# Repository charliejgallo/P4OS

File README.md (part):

# P4OS

An iPhone-style operating system for the
[**Waveshare ESP32-P4-WIFI6-Touch-LCD-5**](https://www.waveshare.com/esp32-p4-wifi6-touch-lcd-5.htm)
([wiki](https://docs.waveshare.com/ESP32-P4-WIFI6-Touch-LCD-5)). It is a 5"
720×1280 touch board with an ESP32-P4 (two RISC-V cores at 400 MHz and
32 MB of PSRAM) and an ESP32-C6 that does the Wi-Fi.

It has a home screen with pages, folders and a dock, a control centre and
notifications, and a lock screen with an optional code, and it runs in
portrait or landscape. There are twenty-three built-in apps and forty-six more on
the microSD, loaded as shared objects:

- **Games:** twenty-four, among them Mila (a Sokoban with a black cat in
  Blender 3D), Monster Hop, a racing game, golf, a robot RPG, a 3D pinball
  with six tables, a pipes game with six liquids, Doom at 35 fps and Duke
  Nukem 3D; and an emulator of
  fourteen consoles, the Game Boy Advance and the Neo Geo at full speed.
- **Tools:** notes with task lists, a street map with offline zones,
  internet radio, IP cameras, video, a 3D viewer, a tuner, a drawing app,
  a VNC viewer for a computer's screen, every 3D printer in the house
  (OctoPrint, PrusaLink, Bambu Lab, Klipper, Duet, Elegoo, FlashForge,
  Creality) with its camera, a computer algebra system with
  graphs, geometry and statistics, a data logger for the header's sensors,
  Lua, and Python (MicroPython).
- **A web portal** for files, updates, the log and the network sweeps, and a
  page for every app that wants one, which the app brings from the card.
- **Bluetooth with the phone:** the iPhone's notifications on the board, in
  colour emoji, its music, and its calls answered or rejected from the
  board; and the board as a computer's wireless keyboard and mouse.
- **USB:** the port becomes a keyboard, mouse, gamepad, MIDI device, network
  or disk for a computer; and the board is a USB host on its 40-pin header,
  two ports at once: pendrives, keyboards, mice, gamepads, webcams, sound
  cards, MIDI and serial devices.
- **A Wi-Fi network of its own,** joined with a QR code.
- **Ethernet, for a board that has the module:** a W5500 on the header,
  and tools for a wired bench: a tester for a network port, finding a
  device of unknown address, a capture for Wireshark.
- **The workshop:** I2C, SPI, 1-Wire and GPIO on the 40-pin header, with
  112 kinds of sensor read by themselves (temperature, pressure, air
  quality, light, motion, current, distance...), addressable LED strips on
  any free pin (WLED's way), a serial terminal, an ESP32, Arduino and SWD programmer,
  RS485 with a Modbus tester (master, slave, monitor, a TCP gateway) and
  DMX512 (a test console, an analyzer, RDM, an Art-Net and sACN node, and a
  lighting console for a phone), a bench supply and scope, an EEPROM reader and writer, a PWM and
  servo generator with an analog level (and sixteen more servos on a
  PCA9685), a learning
  infrared remote with SmartIR's codes, and a CAN bus analyser. Each one
  was tried on the bench with real parts, wiring diagrams and photos
  included.
- **A software radio:** an RTL-SDR stick on the USB host gives a live
  spectrum and waterfall, broadcast FM in stereo, AM for the airband and
  narrow FM for hams and PMR, and the 433/868 MHz remotes and weather
  sensors decoded, with recordings of all of it and a page in the portal.

A desktop simulator runs the same UI code, so most of it can be built and
tried without the board.

It descends from [AmoledOS](https://github.com/charliejgallo/ESP32S3_AmoledOS),
a smartwatch firmware for a 1.8" board. The app model, the portal and many
of the apps came from there, redrawn for a screen five times larger.

<p align="center"><em>The captures come from the simulator, which draws the
same pixels as the board.</em></p>

<p align="center"><em>And on the board: a BME280 on the rear header, found by
itself in Modules and by the scan in Bus, and the SPI loopback at 40 MHz
(that one is a capture from the panel, over HTTP).</em></p>

<p align="center"><em>A MAX6675 with a type K thermocouple on the SPI port:
Bus's example reads it, and Modules logs it every second; the curve is the
tip heated with a lighter.</em></p>

<p align="center"><em>A Pimoroni BME688 on i2c.ext: Bus lists what may live at
0x76, and Modules recognises it by itself as a BME688 (not a BME680), with
its gas resistance, which fell to half with alcohol near it and came back.</em></p>

<p align="center"><em>An SCD41 found by itself at 0x62: the chart is the CO2
of a breath on it, from 3000 ppm back to the room's 600.</em></p>

<p align="center"><em>The Programmer reading the whole flash of an AmoledOS
watch (an ESP32-S3 on its own USB) to the card, and writing it back: the
watch came back with every setting it had.</em></p>

<p align="center"><em>And by SWD, three wires to a Pico's debug header: the
RP2040 found behind its multidrop port and a new firmware written and
verified in under half a second.</em></p>

<p align="center"><em>A cheap Wi-Fi camera (a Hi3518EV200) opened up, its
console pads soldered to the header: U-Boot stopped with a mix of keys and its
16 MB read out through its own commands, twice, with the same SHA-256 -
the copy kept before giving it a new firmware.</em></p>

<p align="center"><em>The Ekoparty 2026 badge (an nRF52840 running
Meshtastic) read whole by SWD in 8 seconds, and an Arduino Nano from a
drawer on the USB host: written by the Programmer, then talking in the
Terminal.</em></p>

<p align="center"><em>A Blue Pill by SWD: its chip a clone (DPIDR 2BA01477,
a CKS32) with 128 KB that really are there. Read whole in a second, written
and erased; and the same again through ST's serial bootloader on the same
two wires.</em></p>

<p align="center"><em>An ESP32 DevKit on the header with six wires: the
board resets it into its ROM by itself and writes it at up to 921600 baud;
the Mac's esptool does the same through the board's bridge.</em></p>

<p align="center"><em>The same Nano, now on the header: its 5 V TX through
a divider, the EN line on its reset. Written and read by the Flasher, and
by avrdude on the Mac through the bridge.</em></p>

<p align="center"><em>A Mega 2560 from an old 3D printer and a Pro Micro on
the USB host: the Mega's own bootloader, and the Pro Micro's, reached with
the 1200-baud touch.</em></p>

<p align="center"><em>An Arduino Yún: its Linux in the Terminal through the
32U4, and its old U-Boot (no sf, no crc32, a big-endian MIPS) read whole by
the Programador, the same MD5 its Linux gives.</em></p>

<p align="center"><em>Ethernet: a W5500 Lite on the header with six loose
wires, and Network's Cable tab telling what the port it is plugged into
gives (the network's addresses are blurred).</em></p>

---

## What it does

### The shell

The home screen has icon pages, folders, a dock and widgets.

- **Arranging it** is as on an iPhone. A long press starts edit mode, where
  a swipe still turns the page and an icon held still for a moment drags:
  - onto another page;
  - onto another app, to make a folder;
  - into a folder;
  - in or out of the dock, where the icons drag the same way.

  Folders show twelve apps a page, and a swipe turns one whole page. The
  portal's `#inicio` page does the same from a computer.

- **Widgets** (on the board since 0.22.0): edit mode's **+ Widget** adds
  the clock, the sensors, Home Assistant, the system monitor or Claude's
  usage; a tap on a widget opens its sheet, with its size (2×2, 4×2, 4×4),
  what it shows and a way to take it off, and one held still for a moment
  drags like an icon. The **sensors widget** shows up to six of the sensor
  service's values (on its own CO₂, temperature, humidity, pressure and the
  like; CO₂ and particles coloured by their level), the **Home Assistant**
  one up to eight entities, the favourites or the ones picked.

- **Swiping down** from the top opens the control centre (Wi-Fi, Bluetooth,
  do not disturb, the system sounds, orientation, brightness, volume, the
  music playing on the board or on the iPhone, the screen recording) and the
  notifications, with the phone's own actions.
- **System sounds:** a few notes of the speaker's bell when locking and
  unlocking, for notifications and calls, screenshots and recordings, and an
  optional keyboard click. The control centre's bell turns them all off.
- **Recording the screen** (since 0.21.5): the control centre's Grabar
  button records what the panel shows to an MP4 on the card (`/videos`),
  games and cameras included, with a red dot in the status bar while it
  runs. The P4's own engines do the work: the PPA turns each frame into
  the encoder's YUV, the hardware H.264 encoder compresses it (70 ms a
  frame between them, 15 fps on a quiet screen and 7-9 while apps move),
  and the CPU mostly waits. It plays on a Mac or a phone as it is.
- **Typing** (since 0.24.0): the field being edited shows a blinking cursor
  and a ring in the accent colour. The keyboard has an ñ, holding a key
  opens its accents (á, ü, ñ, ¿...), shift gives one capital or locks with
  two taps, and dragging along the space bar moves the cursor. Holding a
  field selects, cuts, copies and pastes; the clipboard is shared with the
  apps and with the portal, which can type a long password or an address
  straight into the field open on the board.
- **Search** (since 0.24.0): a swipe down from the middle of the home screen
  finds apps, the pages of Settings, notes by their text and the card's
  files, and works out a sum typed in.
- **The status bar** shows the Wi-Fi or the board's own network, the card
  and the USB.
- **The orientation** is chosen in Settings or the control centre, because
  the board has no accelerometer. Apps that only make sense one way turn the
  screen while they are open.
- **The BOOT button** goes home with a tap and takes a screenshot with a long
  press; screenshots go to an album in Photos. Held during the boot screen,
  it starts in safe mode, without the card's apps.

| Settings in landscape | Macro pad | Photos |
|---|---|---|
|  |  |  |

<p align="center">
  
</p>

<p align="center"><em>Recorded by the board itself with its control
centre's button: the home screen, a folder, Photos.</em></p>

### The lock screen

It shows the time and date large, the messages that came in, and the music
playing with its buttons, over the wallpaper. To unlock, swipe up from
anywhere: the screen follows the finger.

- **When it locks:** at boot, and when the screen has been off for the time
  chosen in Settings (as soon as it goes off, or 1, 5, 15 or 60 minutes
  later). It is checked while the screen is still dark, so waking never
  shows a frame of what was under it.
- **An optional code** of 4 or 6 digits. It is kept as a salted SHA-256,
  never as itself. After 5 wrong tries the pad waits 30 s, and twice as long
  every 3 more; the count survives a restart.
- **A forgotten code:** in the BOOT button's safe mode the lock screen
  does not ask for it, and Settings can remove it.
- **Messages:** today the apps' notifications; the phone's over Bluetooth and
  Home Assistant's will arrive in the same list. With a code, their text can
  stay hidden until unlocked.

| Locked | The code | Settings, Wi-Fi: its own network |
|---|---|---|
|  |  |  |

### Wallpapers

Eight gradients and a ninth that follows the time of day (night, dawn, day,
dusk, a little different every minute), and over them a photo from the card for the home screen
and another for the lock screen, chosen from Photos (the palette at the top
right of a photo). Each is cropped to the screen, kept in PSRAM (1.8 MB a
screen, nothing in internal RAM) and darkened as much as its own
brightness asks, once, while it is decoded, so the white names read on it
with no translucent layer to blend each frame. Turning the screen crops it
again; Settings, Wallpaper shows which photo each has and removes it.
The lock screen can take a whole folder instead (since 0.22.0): another of
its photos, at random, every time the board locks. The home screen's photo
stays in PSRAM with an app in front, so going home shows it at once; the
lock screen's is let go and decoded again as the screen goes dark.

| Home, over a photo | Locked, over another |
|---|---|
|  |  |

<p align="center"><em>Both on the board, both of Mila.</em></p>

The same page picks the **accent colour** (switches, selections, the active
buttons), one of iOS's nine system colours. The lock screen's clock is
large or medium, at the top or in the middle, and white, the accent, or the
lock photo's own colour lightened (Settings, Lock screen).

The gesture is a free swipe up, as phones do it today, and not a control
dragged along a track: Apple's 2005 patent on the latter
([US 7,657,849](https://patents.google.com/patent/US7657849B2)) expired in
2025, but that is not the reason this one was chosen.

### Built-in apps

Every day:

| Files | Photos | Music | Clock | Calendar |
|---|---|---|---|---|
|  |  |  |  |  |

| Calculator | Converter | Home Assistant | Claude | Monitor |
|---|---|---|---|---|
|  |  |  |  |  |

- **Files:** the card's explorer, with search, copy, move and folders, and
  firmware opened straight in the Programmer.
- **Photos:** albums, the screenshots among them.
- **Music:** MP3, gapless, with the covers.
- **Clock:** world clock, alarms, stopwatch, timer and pomodoro.
- **Home Assistant:** favourites and the calendar, over its WebSocket API.
- **Claude:** the usage of your own Claude plan, the numbers Claude Code's
  `/usage` shows. It is unofficial; see [CLAUDE-APP.md](docs/CLAUDE-APP.md).
- **Monitor:** CPU per core, the tasks, memory, temperature and the network.
- **Also built in:** MQTT, Conway's Life, and Network, which has its own
  section below.

### Network, the tools for a network

Red in Spanish. Seven tabs; the first four work over any network, the
next two are for the wire ([Ethernet](#connected)), and the last for both.

| Cable | The switch, the traffic | Device | One device | Lookout |
|---|---|---|---|---|
|  |  |  |  |  |

- **Ping, Hosts, WiFi, mDNS:** latency and loss charted; a sweep of the
  network with every MAC and its maker, and a port scan; the Wi-Fi
  channels; the services announced. Each sweep is saved, and the portal
  compares it with the one before.
- **Cable** (since 0.27): a tester for the network port the board is
  plugged into.
  - What the port gives: speed and duplex, the address, the DHCP server
    and its lease.
  - "Test the way out": the gateway, a name, the internet, one after the
    other.
  - The switch: a managed one says its name, the port and the VLAN this
    cable goes to (LLDP or CDP).
  - "Compare": ten pings to the gateway by the wire and ten by the Wi-Fi,
    side by side. "Measure the speed" counts what `iperf -c` sends from a
    computer.
  - "Capture to the card": every frame that reaches the port, in a pcap
    file for Wireshark, and a warning for what a network should not have:
    two DHCP servers, one address claimed twice, a broadcast storm.
- **Device** (Equipo, since 0.27): for a device plugged straight into the
  board, its address unknown.
  - It listens: a device gives itself away as it starts (ARP, DHCP, mDNS,
    NetBIOS, SSDP, WS-Discovery). A sweep by ARP of the networks devices
    come set to finds the one that says nothing.
  - A tap opens the device: everything it said, who made its network card
    (with the IEEE's register on the card), a ping, a scan of its ports,
    and "Get on its network", which gives the wire an address next to its
    own.
  - The bench network: the board gives addresses out by DHCP, serves
    files by TFTP, the time by NTP and takes the device's syslog, on the
    wire only. "Share the Wi-Fi" also gives the device a way out through
    the board's Wi-Fi.
- **Lookout** (Vigía, since 0.27): a list of the bench's devices, which
  are on (a ping or a TCP port, every ten seconds while the tab is open),
  and Wake-on-LAN for the ones that are off.

What ran on the board and what did not is under
[What was tested](#what-was-tested-and-what-not-yet);
[docs/MODULES.md](docs/MODULES.md), "Ethernet", has each tool.

### The workshop

The 40-pin rear header is described in `modules.txt`: which pins make each
port (`i2c.ext`, `spi.a`, `uart.*`, GPIO) and which modules hang from them.
While an app uses a port it owns it, and Settings, Expansion draws the
header with who holds each pin.

The whole header, pin by pin, is under [The hardware](#the-40-pin-header).

| Bus (I2C scan) | Modules | Terminal | Programmer | Equipos (Riden) | Electronics |
|---|---|---|---|---|---|
|  |  |  |  |  |  |

- **Bus:** scans I2C and names what answers, talks to SPI chips with presets
  (flash memories, the MAX31855 and MAX6675 thermocouples, the MCP3008, the
  RC522 RFID reader, a loopback), finds the DS18B20s on a 1-Wire bus and reads them live with
  their resolution, and reads and drives GPIO.
- **LED Strips:** an addressable strip (WS2812B, WS2811, SK6812, SK6812 RGBW)
  on any free pin of the header, with the colour order and the number of
  LEDs. It has 13 effects with speed, intensity and two colours. The power
  tab estimates what the strip draws, WLED's way, and dims the whole frame to
  stay within the supply's budget. The strip keeps running with the app
  closed and comes back after a restart.
- **Modules:** live readings from 112 kinds of sensor, every second with
  five minutes of history (since 0.20): temperature and humidity, pressure,
  air quality (CO2, VOC, particles), light and colour, motion and compass,
  voltage and current, distance and presence. The I2C ones that can tell
  who they are are found by themselves (BME280/680, SHT, AHT, SCD4x, SGP30,
  VEML7700, TSL2561, TCS34725, MPU-9250, BNO055, INA219/226/260, ADS1115,
  VL53L0X...); the rest are added from a form: thermocouples and PT100s on
  SPI, DS18B20s on 1-Wire, DHT22, HC-SR04, HX711 scales, flow meters and
  PIRs on plain pins, MH-Z19, PMS5003, PZEM-004T and LD2410 radars on a
  serial port. Every app reads them by name (`aos_sensors.h`); the
  catalogue is [docs/SENSORS.md](docs/SENSORS.md).
- **Terminal:** two serial ports, hex, filters and alerts.
- **Programmer:** flashes another ESP32 from firmware on the card
  (esp-serial-flasher), wired to the header or plugged into the USB host
  (a dev board goes into its bootloader by itself, through RTS and DTR);
  reads its flash to the card, to keep or to clone, and erases it. The
  same for an AVR Arduino through the bootloader it already has (Uno,
  Nano, Pro Mini, Mega, Leonardo, Micro), from the `.hex` the Arduino IDE
  exports. And by SWD, on the same pins: an nRF52, an RP2040, an RP2350,
  an STM32 (F0, F1, F2, F4 like the Black Pill, G0, G4, L4), a SAMD21 or
  SAMD51 (Arduino Zero and MKR, Adafruit M0 and M4, Seeed XIAO, their
  bootloader kept) or a SAM3X (an Arduino Due) written, verified and read
  to the card, its read protection taken off by erasing it, and the RTT
  console of the firmware running on it. Anything with U-Boot on a
  serial console - an IP camera, a router, a set-top box - has its
  whole flash read out through U-Boot's own commands, each piece checked
  by U-Boot's CRC, and nothing written. Or an STM32 through its own serial bootloader, with
  BOOT0 and NRST on the same lines an ESP32 uses. And it lends its port to
  the computer: esptool over `rfc2217://p4os.local:4000`, avrdude over
  `net:p4os.local:4001`; or becomes its CMSIS-DAP debug probe on the OTG
  connector, for OpenOCD, pyOCD and probe-rs.
- **Modbus** (on the card since 0.25.0): a tester for Modbus RTU on RS485.
  A master (any function, once or live; find the units on a bus, and its
  speed and format, the format by the line's parity and framing errors),
  a slave with faults on demand (silent, slow, broken CRC, busy) that also
  serves Modbus TCP, and a monitor that only listens. Device profiles as
  CSV (six examples; Home Assistant and ESPHome YAML imported on the
  portal), so a master reads "Temperatura 23.4 °C" and a slave plays the
  device. A TCP → RTU gateway for a PC program or a SCADA, every frame in
  hex and in words, and the portal page drives it all.
- **Equipos:** the Riden RD60xx supply over RTU and a DOMCOM gateway, out
  of the old Modbus app.
- **DMX** (0.25.0): DMX512 on the same RS485 port. A test console (512
  faders, a chase to find channels, the packet's shape), a fixture the
  board plays, an analyzer with the BREAK and MAB measured on the pin, an
  Art-Net and sACN node (the network out as DMX, ArtPoll answered), and
  RDM: the fixtures on the line found by discovery, their address and name
  set, identify.
- **Luces** (0.25.0): a lighting console. Fixture types (twelve built in,
  more as CSV), a patch in four universes, a programmer for the selected
  fixtures (intensity, colour, strobe, a pan/tilt pad), groups, effects and
  three test modes, scenes with their own fade, a chase with tap tempo;
  universe 1 on RS485 and all of them as Art-Net. Its portal page is a
  second console for a phone.
- **Bench:** a Rigol scope over the LAN, the Riden, a UNI-T generator over
  USB, and a logger to CSV.
- **Electronics:** resistor colours, Ohm's law, dividers, LEDs, the 555 and
  SMD codes.

The simulator has fake chips and fake servers for all of it: every one of
the 112 sensors has an emulated twin that speaks its protocol
([docs/SENSORS.md](docs/SENSORS.md), [docs/MODULES.md](docs/MODULES.md)).

| LED Strips: effects | The strip | Power | Bus: 1-Wire |
|---|---|---|---|
|  |  |  |  |

**From the card, for the bench** (since 0.10). Each one owns the header
pins it uses, has a wiring drawing on the board and a page in the portal.

| EEPROM | PWM | Infrared | CAN |
|---|---|---|---|
|  |  |  |  |

- **EEPROM:** reads, writes and edits serial memories: 24xx on I2C, 25xx
  and 25Qxx flash on SPI, 93xx Microwire. It finds the chip and measures
  its size, has a hex editor with find and undo, keeps versions with CRC32
  and MD5, compares them, and draws the wiring for the chosen chip.
- **PWM:** seven channels on any free pins, from 1 Hz to 20 MHz, with a
  knob, patterns (ramp, breathing, strobe, sine), servo pulses in
  microseconds, and an analog level through an RC filter (the P4 has no
  DAC). Since 0.20, sixteen more on each PCA9685 module over I2C, for
  servos and LEDs.
- **Infrared:** learns a remote's buttons (NEC, Samsung, Sony, JVC,
  Panasonic, RC5, RC6, or raw) and sends them back; air conditioners, TVs, fans and lights
  from [SmartIR](https://github.com/litinoveweedle/SmartIR)'s code library.
- **CAN:** a bus analyser on the P4's TWAI controller: frames live, by id,
  sending, decoding signals, and recording to the card. The signals come
  from any `.dbc` in a folder of the card (opendbc's and nberlette/canbus's
  open libraries read as they are), and an OBD-II scanner asks a car the
  PIDs of SAE J1979. It needs a 3.3 V transceiver (SN65HVD230); its self
  test needs none.

Tried on the bench on 2026-10-05: PWM at three frequencies at once with a
servo and the analog level checked with a meter (1.34 V asked, 1.313 V
measured), a WS2812B strip straight from 3.3 V, a monitor's remote learned
and sent back, and a 24LC256 read, edited, written and restored with its
checksums matching on a computer. The wiring drawings and the numbers are
in [docs/MODULES.md](docs/MODULES.md).

<p align="center"><em>A CAN bus on the bench: an ESP32 with an SN65HVD230
playing a car, the P4 with another. Every frame, no errors, and the engine
speed decoded from a .dbc and charted through the gears.</em></p>

Since 0.20 the PWM app also drives the outputs of a PCA9685 over I2C. On
the board, five servos on one module, fed from their own 5 V supply: each
one moved alone first, then all five in a sine wave, each a fifth of a
turn behind the last ([video](docs/media/pca9685-servos.mp4)).

<p align="center">

</p>

### RS485: Modbus, DMX and Luces

Since 0.25, three apps on the card for the header's RS485 port (`uart.a`,
with a 3.3 V transceiver or an automatic "RS485 to TTL" module), each with
a page in the portal (the Modbus, DMX, Luces and Equipos bullets above say
what they do).

| Modbus: a slave playing a profile | Modbus: traffic | DMX: analyzer | DMX: RDM | Luces: stage | Luces: scenes |
|---|---|---|---|---|---|
|  |  |  |  |  |  |

The bench is the P4 and an ESP32 DevKit, each with an automatic module, on
a twisted pair (`tools/rs485_test`): the ESP32 plays a Modbus slave or
master, a DMX console, or a DMX light on a strip of 8 WS2812B pixels that
also answers RDM. On the board: Modbus both ways with thousands of requests
and only the errors played on purpose, the format of a slave found by the
line's errors, DMX at 40 packets a second both ways, RDM finding the ESP32
and moving its address, and Art-Net from a Mac coming out as DMX.

### Datalog

A data logger for the header's sensors (from the card, since 0.19). Each
line is a value written with its date and time to a CSV of its own in
`/datalog`, every N seconds, minutes or hours or at set times: any value
of a sensor of Modules (I2C, SPI, 1-Wire, on pins or serial), a GPIO with
its pull-up or pull-down, an
ADS1115 input in volts or scaled into a unit of your own, or the board's own
Wi-Fi and memory. Low and high alarms, with hysteresis, sound and show over
any app, or only leave a note in the CSV, and can drive a GPIO (a relay).

| The lines | One line's chart | A new line |
|---|---|---|
|  |  |  |

While it logs it works hidden, shows a red dot in the status bar, and
starts by itself with the board, so a power cut or an update does not stop
it; paused, it does not. Its page in the portal (`#datalog`) shows the live
values and the charts and downloads the files. On the board, a MAX6675 and
a DS18B20 logged every 10 s (the captures above);
[apps/datalog/README.md](apps/datalog/README.md) has the rest.

### RF, a software radio

An [RTL-SDR](https://www.rtl-sdr.com/about-rtl-sdr/) stick (an RTL2832U with
any of the tuners osmocom's library knows, the RTL-SDR Blog V4 included)
plugged into the USB host, with the driver inside the app: the firmware only lends
it raw USB access, so another receiver is another source file in the app
and no firmware ([apps/rf/README.md](apps/rf/README.md)). From the card,
since 0.11.

| FM, listening | 433 MHz, Data mode | A sensor's details |
|---|---|---|
|  |  |  |

- **Spectrum and waterfall,** up to 2.4 Msps with none lost, drawn
  straight to the panel. Drag to tune, tap a frequency to centre it, or
  type one; a row of bands (FM, airband, marine, 2 m, 433, 70 cm, PMR).
- **Listening:** broadcast FM (mono, with the stereo pilot shown), AM for the
  airband, narrow FM for hams and PMR, with squelch over the measured
  noise floor. The filters are 16-bit fixed point on the P4's SIMD
  (esp-dsp), at about a third of one core.
- **Data:** the on-off keyed signals of 433/868 MHz remotes and sensors
  found in the band, their pulses analysed (PWM, PPM, Manchester) and
  decoded: EV1527 and PT2262 remotes, Nexus and Prologue thermometers;
  anything else shows its timings and bits.
- **Keeping it:** a screenshot, the audio as WAV,
  the raw signal as I/Q (and played back later as if live), what was
  received as CSV, and over MQTT.
- **Its page in the portal:** the spectrum and waterfall live, tuning and
  every control, the received list, the spectrum as PNG, and the
  recordings to download.

On the board, 2026-10-07: two gate remotes, a copier and a factory one,
in Data mode with every button on its line; and the back of the board,
with the two USB host sockets on the header in a 3D-printed cover: "2.0"
is pins 25/27 (High Speed, the RTL-SDR's), "1.1" pins 21/23 (Full Speed).

`librtlsdr` is GPL v2, so `rf.so` is too; the firmware stays MIT
([THIRD-PARTY.md](THIRD-PARTY.md)).

### BLE, a Bluetooth LE scanner

Everything the devices around advertise over Bluetooth LE, heard by the
C6's radio and explained ([apps/ble/README.md](apps/ble/README.md)). The
firmware lends the apps a raw scanner and a GATT client
(`aos_hal_ble_*`, [docs/BLUETOOTH.md](docs/BLUETOOTH.md)); what the bytes
mean is the app's. From the card, since 0.12.

| Nearby | Radar | Sensors | Airwaves |
|---|---|---|---|
|  |  |  |  |

- **Nearby:** each device with what it seems to be (phone, earbuds, watch,
  tracker, thermometer, mouse...), its company, the kind of address, the
  last 30 seconds of signal, and a sensor's readings; sorted and filtered.
- **Radar** by estimated distance, and a **finder** for one device: its
  signal in big numbers, whether it is getting closer, and a beep that
  comes faster as you walk towards it.
- **Sensors:** the readings thermometers and the like broadcast (BTHome,
  pvvx/ATC, Xiaomi's MiBeacon, Govee, Ruuvi, SwitchBot, Qingping, Inkbird,
  Eddystone TLM), with their last two hours, to CSV and MQTT. The ones
  that **encrypt** (a stock Xiaomi, BTHome with a key) are read with the
  device's key.
- **Airwaves:** packets a second, devices, companies, kinds of address and
  of advertisement, the spread of the signal.
- **A device's detail:** every AD structure of its advertisement and scan
  response explained (Apple's Continuity, Microsoft's Swift Pair, Google's
  Fast Pair, beacons, companies, UUIDs), with the raw bytes; and for the
  ones that connect, a **GATT explorer** to read, write and listen to
  their characteristics.
- **Its page in the portal:** the table live (search, sort, CSV and JSON),
  the sensors, a device's packets, and the keys.
- If the phone, the computer or the Wi-Fi goes down while scanning (the C6
  has one radio for all three), it says so under the scan's buttons.

On the board, 2026-10-07: a stock Xiaomi e-ink clock thermometer, its
readings encrypted (MiBeacon v5), read with the key made for it, next to
its own screen.

### CAS, a computer algebra system

[Giac](https://www-fourier.univ-grenoble-alpes.fr/~parisse/giac.html), the
engine of Xcas, as its author ported it to calculators (KhiCAS), built as
an app for the board: exact arithmetic, algebra, calculus, equations,
matrices, behind a touch interface of six views
([apps/cas/README.md](apps/cas/README.md)). From the card, since 0.14.

| Calculate | Graph | Geometry |
|---|---|---|
|  |  |  |

| Statistics | Finance | Sciences |
|---|---|---|
|  |  |  |

- **Calculate:** results drawn as a book prints them (fractions, roots,
  integrals, matrices), a two-dimensional editor with a keypad of
  templates, and a USB or Bluetooth keyboard typing too. Factor, expand,
  solve, differentiate, integrate, limits, series, Laplace, ODEs...
- **Graph:** six functions on the whole screen; one finger pans, two zoom,
  a long press traces. A regression from Statistics goes there with a tap.
- **Geometry:** points, lines, circles, polygons, intersections,
  perpendiculars, bisectors; drag a point and everything built on it
  follows, with lengths, angles, areas and equations exact when they can be
  (4√2, 25/4, 16π).
- **Statistics:** four lists, histogram, box plots, scatter, six
  regressions, seven distributions, t and z tests.
- **Finance:** TVM, French, German and bullet loans with their table,
  rates (TNA, TEA, TEM), NPV and IRR.
- **Sciences:** the periodic table, molar mass, equations balanced (ions
  too) with their stoichiometry, gases, solutions and pH; 41 physics
  formulas that solve for whichever variable is missing; Punnett squares,
  Hardy-Weinberg, a DNA sequence translated.
- **Its page in the portal:** type from the computer, edit the functions,
  bring lists in from a CSV, save the plot as a PNG.

`cas.so` is GPL-3.0-or-later (Giac); the firmware stays MIT
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
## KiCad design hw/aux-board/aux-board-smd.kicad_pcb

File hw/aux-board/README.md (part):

# The auxiliary board for the 40-pin header

A board that plugs onto the header and takes each port of P4OS to a
connector with a name. The plan, the blocks and the two variants are in
[docs/plan/PCB.md](../../docs/plan/PCB.md) (Spanish); the pin map it follows
is [docs/img/pinout.svg](../../docs/img/pinout.svg).

**Where it stands (2026-11-12): a first schematic of both variants, a first
placement of their parts, the first tracks and a trial of the routing that
joined everything but four ground pads; nothing built. The outline
printed in plastic (`fit-test-th-print.svg`) was tried on the P4: the four
holes and the header fit.** Every part
value and footprint is a first choice to review against its datasheet.

- **th**, for a soldering iron: axial resistors, TO-92 transistors, every
  bridge a 2.54 mm jumper. The board is two layers, ordered bare.
- **smd**, for assembly at the factory: 0603 passives, SOT-23 transistors,
  solder bridges, a Qwiic socket and ESD protection on the USB lines. Its
  connectors are the same through-hole ones, soldered by hand afterwards.

RS485 and CAN are not on the board in either: their modules plug onto pin
headers (the automatic "RS485 to TTL" one on 3V3, TX, RX, GND; an
SN65HVD230 on 3V3, GND, CTX, CRX). Ethernet is a "W5500 Lite" module
(HW-884) on two sockets of six.

**There is no second 2x20 socket with the forty pins again** (taken out on
2026-11-11: nothing used it). In its place three headers of four pins:
switched 5 V and ground, 3.3 V and ground, and the three GPIO that no
other connector of the board carries, 35 (a strapping pin) and 37 and 38
(the console's UART). They stand above the 2x20, between the I2C headers
and the SPI one; beside the 2x20 there are only two bulk capacitors, the
5 V one next to its switch. The silkscreen names the header's forty pins
beside their solder joints.

**Supplies and ground are not to be routed thin:** 0.8 mm at least to the
5 V and 3.3 V headers and wherever it fits, 0.5 mm only through a passage
that takes no more. The ground planes join each ground pin by four spokes
of 0.8 mm.

## The Ethernet module's place

The module that answered on the bench (`docs/plan/ETHERNET.md`) has its
pins and its chip on one face and the RJ45 on the other, so on its sockets
it lies chip down with the RJ45 on top, its mouth to the board's right
edge. The silkscreen draws where it lies.

- The two rows are 20.32 mm apart (`ETH_ROWS` in `place.py`), measured.
- Pin 1 of each socket (G and GND) is the pin nearest the RJ45's mouth,
  as on the module. The row G, G, MO, SCK, CS, INT is the upper one.
- The first pin is 7.5 mm from the module's edge on the RJ45 side
  (`ETH_PIN1`), behind the module's two mounting holes: with it the
  module's edge is on the board's and the RJ45 sticks out past it. Found
  with the printed plate on 2026-11-12: the first guess, 2.5 mm read off
  photographs, left the sockets 5 mm too far out. **Tried again that
  evening on a second plate, with the module on it: its pins go into the
  two rows, the RJ45 comes out at the edge and the module's board does not
  stick out past the plate.**
- Under the module there are 8.5 mm (the sockets' height): a resistor, a
  small capacitor or SMD parts fit, a pin header or an electrolytic do
  not. `place.py` refuses a tall part there.

| File | What it is |
|---|---|
| `gen.py` | the board as a list: its parts and the net on each pin, for the two variants |
| `kisch.py` | writes a KiCad schematic from that list, with KiCad's own symbols |
| `aux-board-th.kicad_sch`, `aux-board-smd.kicad_sch` | the schematics, generated: open them in KiCad 10 |
| `place.py` | puts those parts on a board with the P4's outline and holes, with their nets and the silkscreen; it runs under KiCad's Python |
| `aux-board-th.kicad_pcb`, `aux-board-smd.kicad_pcb` | those boards, generated: drafts to look at and to move, with the first tracks (below) |
| `paper-th.svg` | the through-hole board's front at its real size, outline, lettering and pads: printed on paper at 100 %, it is laid on the P4 and the parts are stood on it |
| `autoroute.py` | a trial router: routes the generated board to show where it is hard ("A trial of the routing", below) |
| `fit-test-th.svg`, `fit-test-th-print.svg` | the through-hole board's outline with every hole, 1 unit = 1 mm: a slicer extrudes it into a plate to try the fit on the P4. The second has each hole 0.4 mm wider, for a printer that closes small holes |

| Through-hole | SMD |
|---|---|
|  |  |

*The drafts as KiCad renders them, black as they would be ordered. The
board is the size of the P4's own and sits on its four holes. The
silkscreen names every connector, every pin and every bridge; where each
part goes is a first guess. `place.py` refuses a placement where two parts
overlap or one leaves the board (the USB sockets overhang on purpose).*

## The tracks so far

`place.py` lays what needs no choice, and lays it again every time it runs:

- **A fan-out of the 2x20 header on the front:** every pin that is not
  ground leaves to a column just right of the header, the inner row
  straight and the outer row through the gap above its own row (0.25 mm,
  0.4 mm for 5 V and 3.3 V).
- **Under the header, the back takes no track and no via** (a KiCad rule
  area): the ground pins reach the back plane by the strip each side of
  the two rows.
- **A ground plane on each face.** The files keep the planes unfilled
  (filled, each file is more than twice the size): KiCad fills them with B.

It then asks KiCad for its design rule check on a copy with the planes
filled, and prints what is left:

    routed: 47 track segments and two ground planes; still to join: 118 connections
    design rules: silk_edge_clearance x4, track_dangling x32

Ground is joined everywhere by the planes; 118 connections of the other
53 nets are still to route (128 on the SMD variant). The four silkscreen
warnings are the USB sockets' outlines, which overhang the edge on
purpose, and the 32 dangling tracks are the fan-out, which goes nowhere
yet.

**The boards are generated, so a track drawn by hand in KiCad is lost the
next time `place.py` runs.** While parts are still moving, tracks go in
the script; routing by hand starts once the placement is frozen, and from
then on `place.py` is not run again.

## A trial of the routing (2026-11-12, the router redone on 2026-11-13)

`autoroute.py` routes the generated board by itself, to find where the
placement is hard before anyone routes it for real. It runs under KiCad's
Python in about three minutes and writes `trial-th.kicad_pcb` or
`trial-smd.kicad_pcb`, which are not kept in git: open them in KiCad to
look.

    <KiCad's python3> hw/aux-board/autoroute.py th

It is a maze router on a 0.3175 mm grid that starts on the header's
pin 1: 0.25 mm tracks, 0.8 mm for the supplies (0.5 mm, then 0.25 mm,
where 0.8 finds no room; it says where), 0.6 mm vias, KiCad's default
0.2 mm clearance.

- **The nets negotiate.** Routed one after another, each around the ones
  before, the last nets went the long way round: tracks along the board's
  edges, 94 mm over the direct way for one of them. Now every net is
  first routed as if alone, crossing the others at a price. Then the ones
  that cross are routed again, round after round, while that price goes
  up and the nodes that were fought over stay dearer for everyone, until
  nothing crosses (eighteen rounds on the through-hole board). Each net
  gives way where it costs it least.
- **A turn has a price**, a square corner more than a 45 degree one and a
  hairpin most, so a track runs straight where it can, and it leaves a
  pad by its middle.
- **Ground is the planes' business.** No ground track is laid until the
  planes are filled; then the router reads KiCad's fill, finds the groups
  of ground pads it left apart from the rest, and joins only those.
- Of the header's fan-out, the stubs the routing did not use are left out
  of the trial board.

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
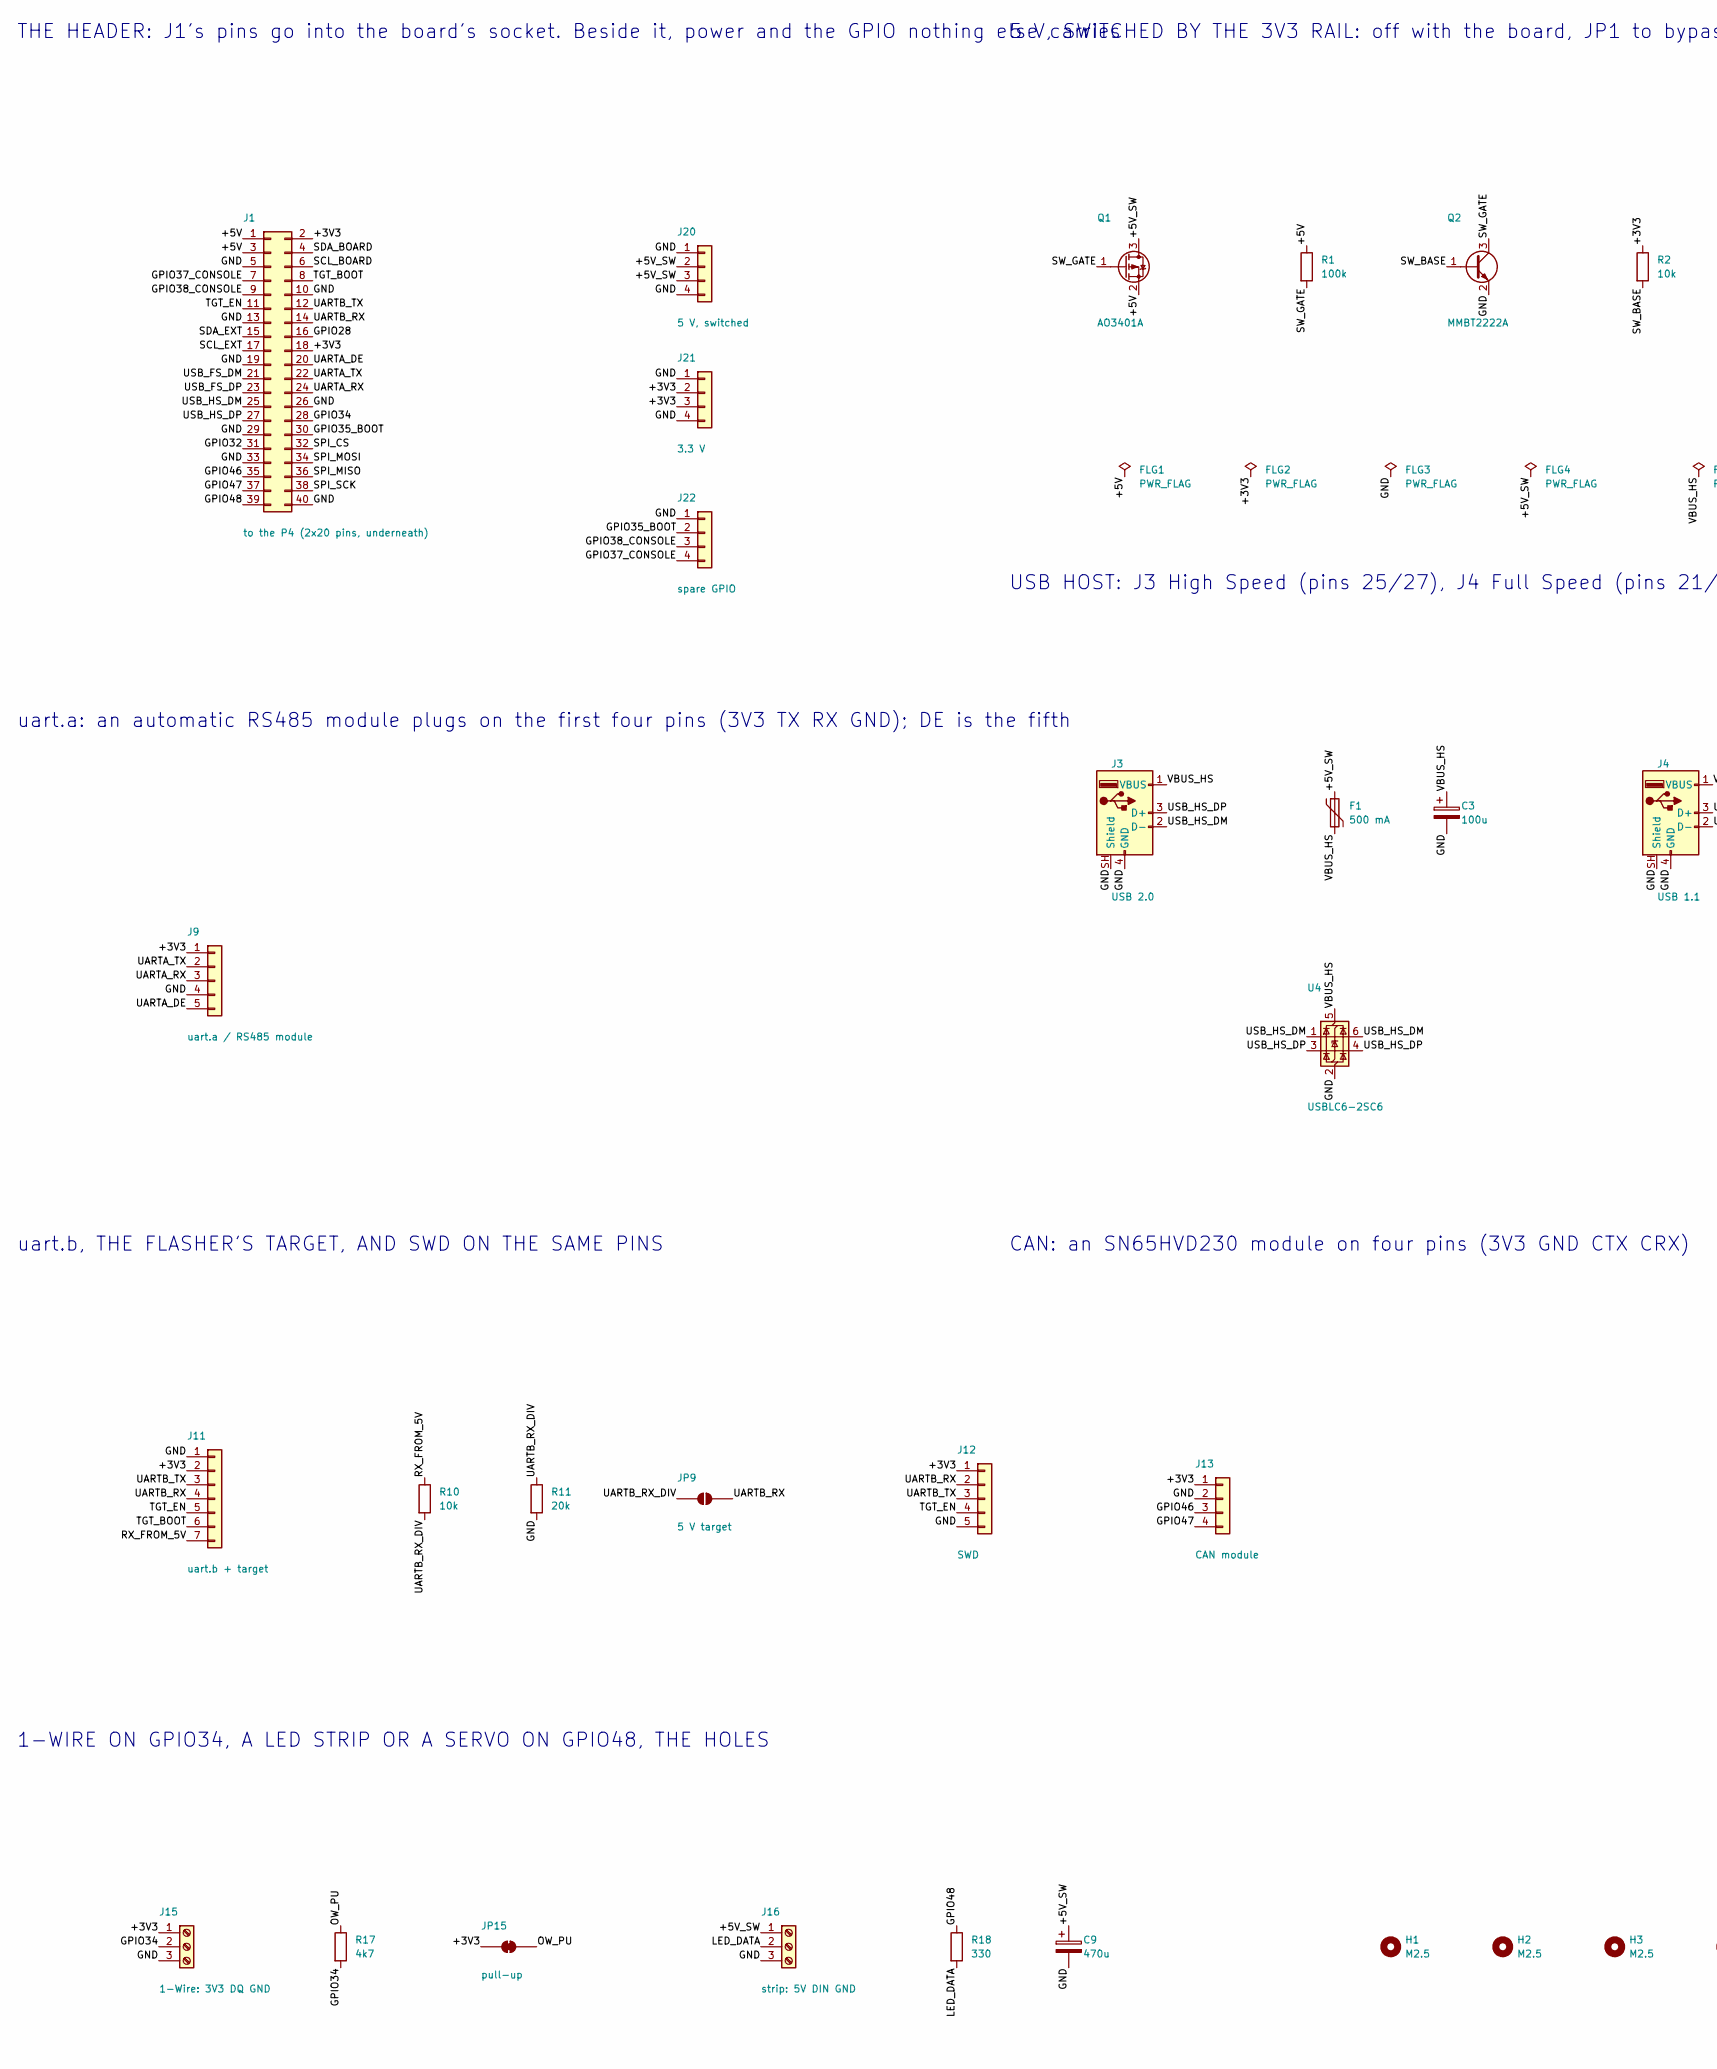
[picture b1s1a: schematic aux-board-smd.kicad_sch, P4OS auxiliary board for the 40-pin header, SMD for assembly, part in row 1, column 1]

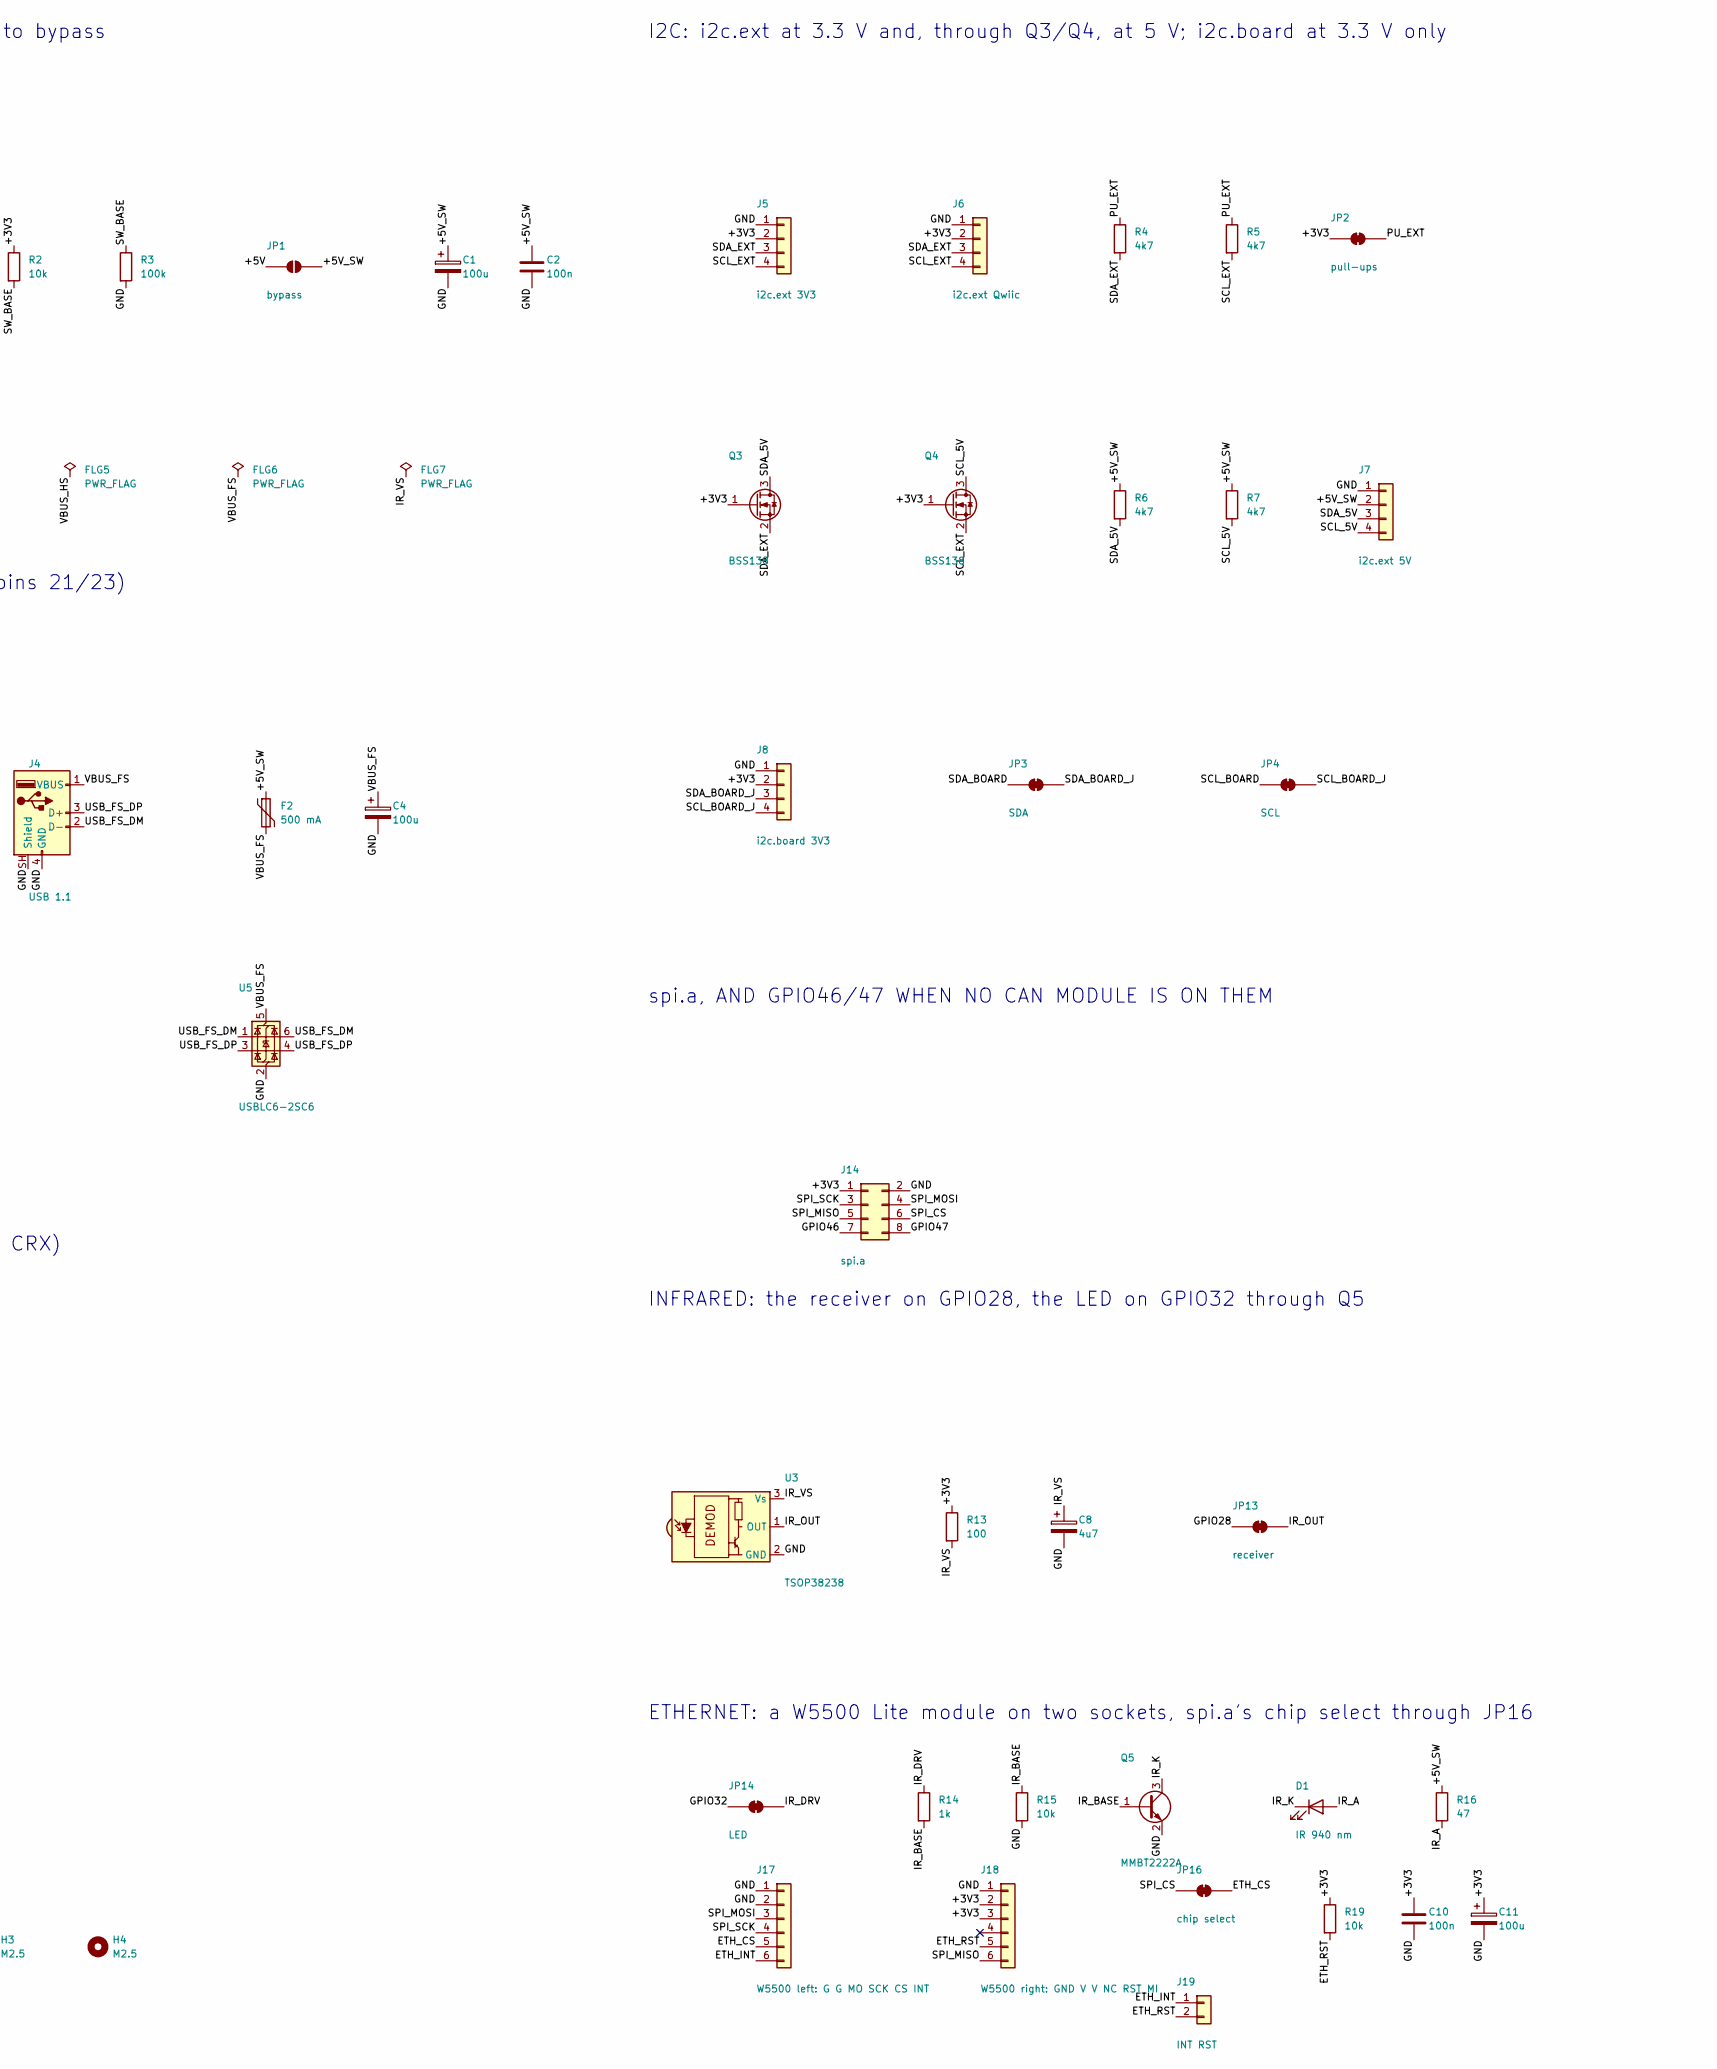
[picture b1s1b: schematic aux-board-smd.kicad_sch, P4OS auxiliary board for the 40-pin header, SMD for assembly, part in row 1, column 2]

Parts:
C1, C3, C4, C11: 100u; CP_Elec_6.3x5.4
C2, C10: 100n; C_0603_1608Metric
C8: 4u7; CP_Elec_6.3x5.4
C9: 470u; CP_Elec_8x10
D1: IR 940 nm; LED_D5.0mm
F1, F2: 500 mA; Fuse_1206_3216Metric
FLG1, FLG2, FLG3, FLG4, FLG5, FLG6, FLG7: PWR_FLAG
H1, H2, H3, H4: M2.5; MountingHole_2.7mm_M2.5
J1: to the P4 (2x20 pins, underneath); PinHeader_2x20_P2.54mm_Vertical
J3: USB 2.0; USB_A_Molex_67643_Horizontal
J4: USB 1.1; USB_A_Molex_67643_Horizontal
J5: i2c.ext 3V3; PinHeader_1x04_P2.54mm_Vertical
J6: i2c.ext Qwiic; JST_SH_SM04B-SRSS-TB_1x04-1MP_P1.00mm_Horizontal
J7: i2c.ext 5V; PinHeader_1x04_P2.54mm_Vertical
J8: i2c.board 3V3; PinHeader_1x04_P2.54mm_Vertical
J9: uart.a / RS485 module; PinHeader_1x05_P2.54mm_Vertical
J11: uart.b + target; PinHeader_1x07_P2.54mm_Vertical
J12: SWD; PinHeader_1x05_P2.54mm_Vertical
J13: CAN module; PinHeader_1x04_P2.54mm_Vertical
J14: spi.a; PinHeader_2x04_P2.54mm_Vertical
J15: 1-Wire: 3V3 DQ GND; TerminalBlock_Phoenix_MKDS-1,5-3-5.08_1x03_P5.08mm_Horizont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
J16: strip: 5V DIN GND; TerminalBlock_Phoenix_MKDS-1,5-3-5.08_1x03_P5.08mm_Horizont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
J17: W5500 left: G G MO SCK CS INT; PinSocket_1x06_P2.54mm_Vertical
J18: W5500 right: GND V V NC RST MI; PinSocket_1x06_P2.54mm_Vertical
J19: INT RST; PinHeader_1x02_P2.54mm_Vertical
J20: 5 V, switched; PinHeader_1x04_P2.54mm_Vertical
J21: 3.3 V; PinHeader_1x04_P2.54mm_Vertical
J22: spare GPIO; PinHeader_1x04_P2.54mm_Vertical
JP1: bypass; SolderJumper-2_P1.3mm_Open_RoundedPad1.0x1.5mm
JP2: pull-ups; SolderJumper-2_P1.3mm_Bridged_RoundedPad1.0x1.5mm
JP3: SDA; SolderJumper-2_P1.3mm_Bridged_RoundedPad1.0x1.5mm
JP4: SCL; SolderJumper-2_P1.3mm_Bridged_RoundedPad1.0x1.5mm
JP9: 5 V target; SolderJumper-2_P1.3mm_Open_RoundedPad1.0x1.5mm
JP13: receiver; SolderJumper-2_P1.3mm_Bridged_RoundedPad1.0x1.5mm
JP14: LED; SolderJumper-2_P1.3mm_Bridged_RoundedPad1.0x1.5mm
JP15: pull-up; SolderJumper-2_P1.3mm_Bridged_RoundedPad1.0x1.5mm
JP16: chip select; SolderJumper-2_P1.3mm_Bridged_RoundedPad1.0x1.5mm
Q1: AO3401A; SOT-23
Q2, Q5: MMBT2222A; SOT-23
Q3, Q4: BSS138; SOT-23
R1, R3: 100k; R_0603_1608Metric
R2, R10, R15, R19: 10k; R_0603_1608Metric
R4, R5, R6, R7, R17: 4k7; R_0603_1608Metric
R11: 20k; R_0603_1608Metric
R13: 100; R_0603_1608Metric
R14: 1k; R_0603_1608Metric
R16: 47; R_0603_1608Metric
R18: 330; R_0603_1608Metric
U3: TSOP38238; Vishay_MINICAST-3Pin
U4, U5: USBLC6-2SC6; SOT-23-6

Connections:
+3V3: C10.1, C11.1, FLG2.1, J1.2, J1.18, J5.2, J6.2, J8.2, J9.1, J11.2, J12.1, J13.1, J14.1, J15.1, J18.2, J18.3, J21.2, J21.3, JP2.1 (A), JP15.1 (A), Q3.1 (G), Q4.1 (G), R2.1, R13.1, R19.1
+5V: FLG1.1, J1.1, J1.3, JP1.1 (A), Q1.2 (S), R1.1
+5V_SW: C1.1, C2.1, C9.1, F1.1, F2.1, FLG4.1, J7.2, J16.1, J20.2, J20.3, JP1.2 (B), Q1.3 (D), R6.1, R7.1, R16.1
ETH_CS: J17.5, JP16.2 (B)
ETH_INT: J17.6, J19.1
ETH_RST: J18.5, J19.2, R19.2
GND: C1.2, C2.2, C3.2, C4.2, C8.2, C9.2, C10.2, C11.2, FLG3.1, J1.5, J1.10, J1.13, J1.19, J1.26, J1.29, J1.33, J1.40, J3.4 (GND), J3.SH (Shield), J4.4 (GND), J4.SH (Shield), J5.1, J6.1, J7.1, J8.1, J9.4, J11.1, J12.5, J13.2, J14.2, J15.3, J16.3, J17.1, J17.2, J18.1, J20.1, J20.4, J21.1, J21.4, J22.1, Q2.2 (E), Q5.2 (E), R3.2, R11.2, R15.2, U3.2 (GND), U4.2 (GND), U5.2 (GND)
GPIO28: J1.16, JP13.1 (A)
GPIO32: J1.31, JP14.1 (A)
GPIO34: J1.28, J15.2, R17.2
GPIO35_BOOT: J1.30, J22.2
GPIO37_CONSOLE: J1.7, J22.4
GPIO38_CONSOLE: J1.9, J22.3
GPIO46: J1.35, J13.3, J14.7
GPIO47: J1.37, J13.4, J14.8
GPIO48: J1.39, R18.1
IR_A: D1.2 (A), R16.2
IR_BASE: Q5.1 (B), R14.2, R15.1
IR_DRV: JP14.2 (B), R14.1
IR_K: D1.1 (K), Q5.3 (C)
IR_OUT: JP13.2 (B), U3.1 (OUT)
IR_VS: C8.1, FLG7.1, R13.2, U3.3 (Vs)
LED_DATA: J16.2, R18.2
OW_PU: JP15.2 (B), R17.1
PU_EXT: JP2.2 (B), R4.1, R5.1
RX_FROM_5V: J11.7, R10.1
SCL_5V: J7.4, Q4.3 (D), R7.2
SCL_BOARD: J1.6, JP4.1 (A)
SCL_BOARD_J: J8.4, JP4.2 (B)
SCL_EXT: J1.17, J5.4, J6.4, Q4.2 (S), R5.2
SDA_5V: J7.3, Q3.3 (D), R6.2
SDA_BOARD: J1.4, JP3.1 (A)
SDA_BOARD_J: J8.3, JP3.2 (B)
SDA_EXT: J1.15, J5.3, J6.3, Q3.2 (S), R4.2
SPI_CS: J1.32, J14.6, JP16.1 (A)
SPI_MISO: J1.36, J14.5, J18.6
SPI_MOSI: J1.34, J14.4, J17.3
SPI_SCK: J1.38, J14.3, J17.4
SW_BASE: Q2.1 (B), R2.2, R3.1
SW_GATE: Q1.1 (G), Q2.3 (C), R1.2
TGT_BOOT: J1.8, J11.6
TGT_EN: J1.11, J11.5, J12.4
UARTA_DE: J1.20, J9.5
UARTA_RX: J1.24, J9.3
UARTA_TX: J1.22, J9.2
UARTB_RX: J1.14, J11.4, J12.2, JP9.2 (B)
UARTB_RX_DIV: JP9.1 (A), R10.2, R11.1
UARTB_TX: J1.12, J11.3, J12.3
USB_FS_DM: J1.21, J4.2 (D-), U5.1 (I/O1), U5.6 (I/O1)
USB_FS_DP: J1.23, J4.3 (D+), U5.3 (I/O2), U5.4 (I/O2)
USB_HS_DM: J1.25, J3.2 (D-), U4.1 (I/O1), U4.6 (I/O1)
USB_HS_DP: J1.27, J3.3 (D+), U4.3 (I/O2), U4.4 (I/O2)
VBUS_FS: C4.1, F2.2, FLG6.1, J4.1 (VBUS), U5.5 (VBUS)
VBUS_HS: C3.1, F1.2, FLG5.1, J3.1 (VBUS), U4.5 (VBUS)

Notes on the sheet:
THE HEADER: J1's pins go into the board's socket. Beside it, power and the GPIO nothing else carries
5 V, SWITCHED BY THE 3V3 RAIL: off with the board, JP1 to bypass
USB HOST: J3 High Speed (pins 25/27), J4 Full Speed (pins 21/23)
I2C: i2c.ext at 3.3 V and, through Q3/Q4, at 5 V; i2c.board at 3.3 V only
uart.a: an automatic RS485 module plugs on the first four pins (3V3 TX RX GND); DE is the fifth
uart.b, THE FLASHER'S TARGET, AND SWD ON THE SAME PINS
CAN: an SN65HVD230 module on four pins (3V3 GND CTX CRX)
spi.a, AND GPIO46/47 WHEN NO CAN MODULE IS ON THEM
ETHERNET: a W5500 Lite module on two sockets, spi.a's chip select through JP16
INFRARED: the receiver on GPIO28, the LED on GPIO32 through Q5
1-WIRE ON GPIO34, A LED STRIP OR A SERVO ON GPIO48, THE HOLES

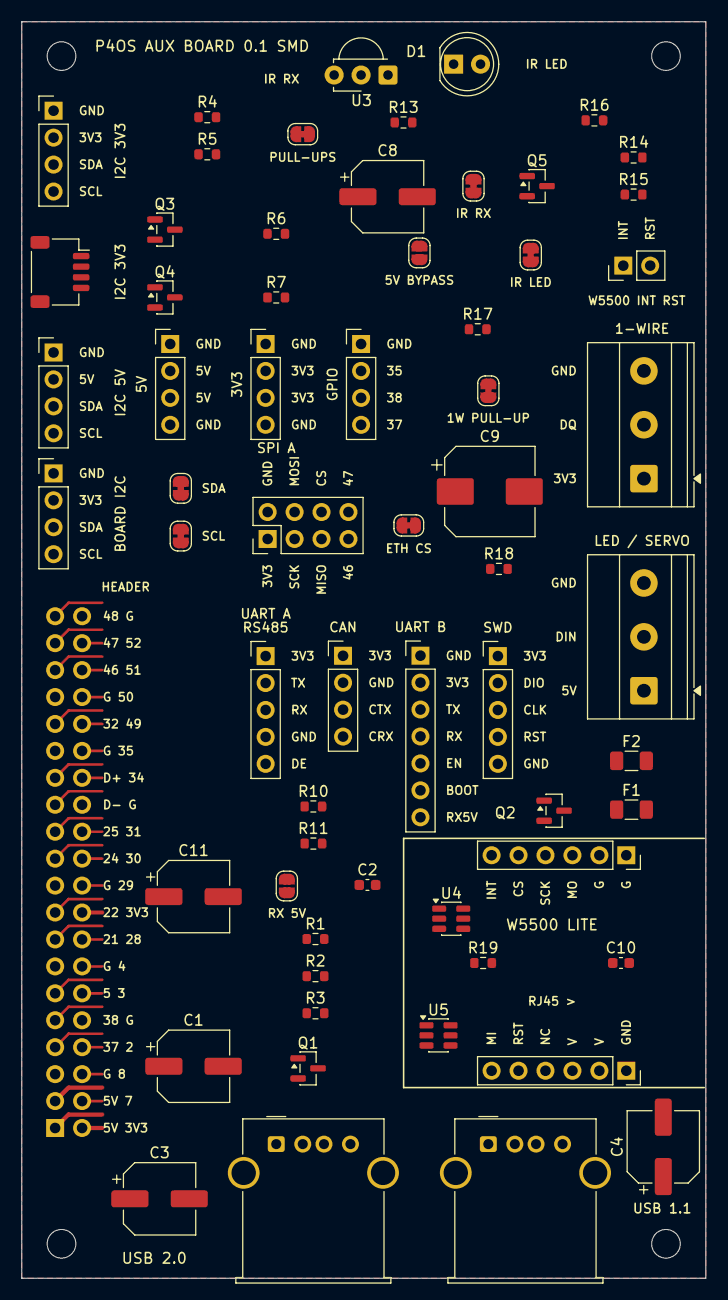
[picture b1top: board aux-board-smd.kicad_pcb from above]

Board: 2 copper layers, 64.5 x 118.5 mm, 68 parts (1 on the bottom side), 54 nets.

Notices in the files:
README.md:
Licence:
MIT, see [LICENSE](LICENSE). Third-party code, fonts, icons and data keep
their own licences; [THIRD-PARTY.md](THIRD-PARTY.md) lists each one and what
it asks for. `apps/doom/` is Chocolate Doom through doomgeneric, under the
GNU GPL v2, and no WAD is included. `apps/duke3d/` is Chocolate Duke3D, under
the GNU GPL v2 and, for its Build engine, Ken Silverman's Build licence; no
GRP is included. `apps/emulador/` keeps each console's core in its own
module under that core's licence (GPL, AGPL, and two non-commercial:
Snes9x and the Mega Drive's Z80), listed in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
